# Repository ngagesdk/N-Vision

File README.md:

# N-Vision

**A modern replacement for the original Nokia N-Gage screen capture hardware.**

## Overview

N-Vision is an open-source hardware project that aims to recreate the functionality
of the extremely rare screen capture device that was once used by Nokia during
promotional events, game demonstrations, and for recording official N-Gage gameplay
footage.

As original capture units have become virtually impossible to find, preserving and
showcasing N-Gage software has become increasingly difficult. N-Vision provides a
modern alternative by tapping directly into the display interface without requiring
any modifications to the console itself.

The project uses a custom flexible PCB (FPC) that is installed between the N-Gage's
mainboard and LCD, allowing the display signals to be captured transparently.
A Raspberry Pi Pico 2 then decodes the display data in real time and outputs it over
DVI, making it suitable for recording, streaming, or development purposes.

## Features (Planned)

- Non-destructive installation using a custom flexible PCB
- Real-time LCD signal capture
- Display decoding on a Raspberry Pi Pico 2
- Digital DVI video output
- Open-source hardware and firmware
- Designed specifically for the Nokia N-Gage Classic

## Project Structure
 
| Directory              | Description                                                                                             |
| :--------------------- | :------------------------------------------------------------------------------------------------------ |
| [decoder/](decoder/)   | Proof-of-concept decoder to toy around with display signals.                                            |
| [firmware/](firmware/) | Firmware for the Raspberry Pi Pico 2 that captures and decodes the N-Gage display signals in real time. |
| [hardware/](hardware/) | Hardware design files for the custom flexible PCB that interfaces with the N-Gage display.              | 

## Project Status

> **This project is currently under active development and is not yet complete.**

The hardware, firmware, and documentation are all works in progress. Expect incomplete
features, design changes, and occasional breaking updates as development continues.

## Contributing

Contributions are warmly welcomed.

Whether you have experience with hardware design, embedded development, reverse
engineering, signal analysis, documentation, or simply own test hardware, your help
is greatly appreciated. Every contribution helps move the project closer to becoming
a practical and accessible replacement for the original capture hardware.

If you'd like to contribute, feel free to open an issue, start a discussion, or submit
a pull request.

## Goals

- Preserve the ability to capture authentic Nokia N-Gage gameplay.
- Provide an affordable and reproducible alternative to the original Nokia capture
  hardware.
- Document the N-Gage display interface for future preservation efforts.
- Build an open platform that the community can improve and extend.

## License

N-Vision is released under a dual-license model:

- **Software** (firmware, utilities, and related source code) is licensed under the
  [**MIT License**](firmware/LICENSE.md).
- **Hardware** (schematics, PCB layouts, mechanical designs, and other hardware design
  files) is licensed under the
  [**CERN Open Hardware Licence Version 2 - Permissive (CERN-OHL-P v2)**](hardware/cern_ohl_p_v2.txt).

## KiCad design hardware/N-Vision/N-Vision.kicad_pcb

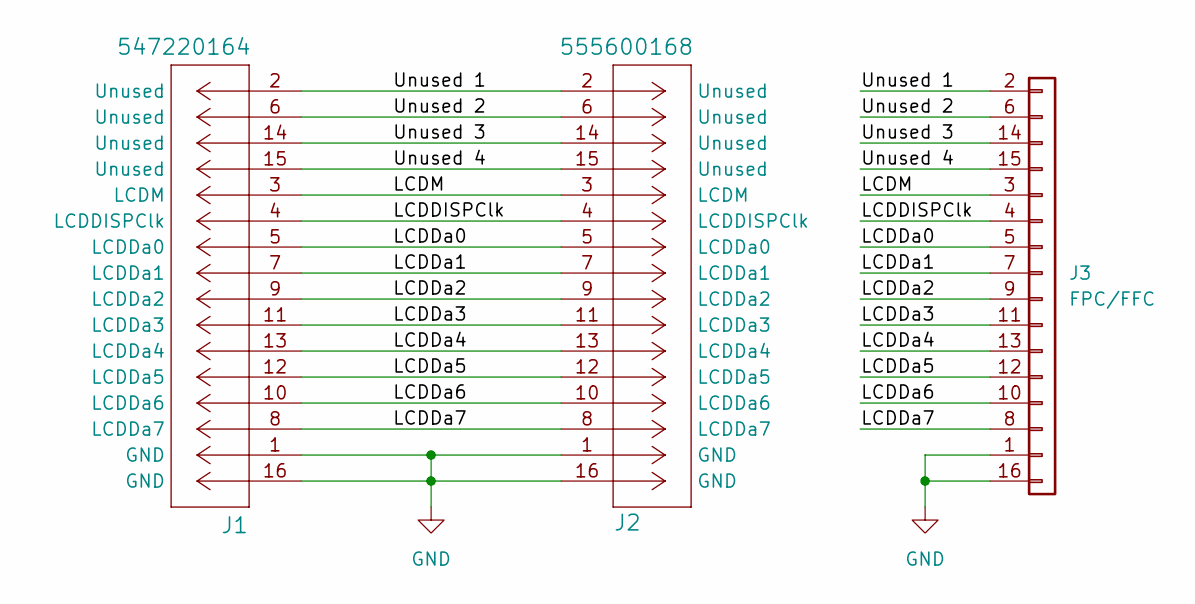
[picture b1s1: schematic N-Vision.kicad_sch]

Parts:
J1: 547220164; CONN_54722-0164_MOL
J2: 555600168; CONN_55560-0168_MOL
J3: FPC/FFC; FPC-16P-0.5mm

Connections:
/LCDDISPClk: J1.4 (LCDDISPClk), J2.4 (LCDDISPClk), J3.4
/LCDDa0: J1.5 (LCDDa0), J2.5 (LCDDa0), J3.5
/LCDDa1: J1.7 (LCDDa1), J2.7 (LCDDa1), J3.7
/LCDDa2: J1.9 (LCDDa2), J2.9 (LCDDa2), J3.9
/LCDDa3: J1.11 (LCDDa3), J2.11 (LCDDa3), J3.11
/LCDDa4: J1.13 (LCDDa4), J2.13 (LCDDa4), J3.13
/LCDDa5: J1.12 (LCDDa5), J2.12 (LCDDa5), J3.12
/LCDDa6: J1.10 (LCDDa6), J2.10 (LCDDa6), J3.10
/LCDDa7: J1.8 (LCDDa7), J2.8 (LCDDa7), J3.8
/LCDM: J1.3 (LCDM), J2.3 (LCDM), J3.3
/Unused 1: J1.2 (Unused), J2.2 (Unused), J3.2
/Unused 2: J1.6 (Unused), J2.6 (Unused), J3.6
/Unused 3: J1.14 (Unused), J2.14 (Unused), J3.14
/Unused 4: J1.15 (Unused), J2.15 (Unused), J3.15
GND: J1.1 (GND), J1.16 (GND), J2.1 (GND), J2.16 (GND), J3.1, J3.16

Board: 2 copper layers, 3 parts (2 on the bottom side), 15 nets, no tracks yet.

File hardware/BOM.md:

# Bill of materials

- [Molex 0555600168](https://www.molex.com/molex/products/part-detail/pcb_headers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  ([Digi-Key](https://www.digikey.com/short/nrwqm2ht))
- [Molex 0547220164](https://www.molex.com/molex/products/part-detail/pcb_recepta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 ([Digi-Key](https://www.digikey.com/short/298jd1bj))
- [Molex 5051101692](https://www.molex.com/en-us/products/part-detail/5051101692) ([Digi-Key](https://www.digikey.de/short/q1pv8zdh))

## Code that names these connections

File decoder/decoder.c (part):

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 *
 * ====================================================================== */
#define CH_LCDCLK 9  /* CSV column wired to LCDCLK                        */
#define CH_LCDM   1  /* CSV column wired to LCDM   (bus bit 7, mode flag) */
#define CH_LCDDa7 11 /* CSV column wired to LCDDa7 (bus bit 8)            */
#define CH_LCDDa6 12 /* CSV column wired to LCDDa6 (bus bit 6)            */
#define CH_LCDDa5 13 /* CSV column wired to LCDDa5 (bus bit 5)            */
#define CH_LCDDa4 6  /* CSV column wired to LCDDa4 (bus bit 4)            */
#define CH_LCDDa3 5  /* CSV column wired to LCDDa3 (bus bit 3)            */
#define CH_LCDDa2 4  /* CSV column wired to LCDDa2 (bus bit 2)            */
#define CH_LCDDa1 3  /* CSV column wired to LCDDa1 (bus bit 1)            */
#define CH_LCDDa0 2  /* CSV column wired to LCDDa0 (bus bit 0)            */

/* -----------------------------------------------------------------------
 * LCD bus signals:
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 *   LCDLLClk   0x75 – line-latch clock  (followed by target-row data words)
 *   LCDDISPClk 0x5C – display pixel clock (followed by pixel data words)
 * ----------------------------------------------------------------------- */
#define LCDM   0x80u /* LCDM mode flag (separate signal) */
#define LCDDa7 0x80u /* bit 7 */
#define LCDDa6 0x40u /* bit 6 */
#define LCDDa5 0x20u /* bit 5 */
#define LCDDa4 0x10u /* bit 4 */
#define LCDDa3 0x08u /* bit 3 */
#define LCDDa2 0x04u /* bit 2 */
#define LCDDa1 0x02u /* bit 1 */
#define LCDDa0 0x01u /* bit 0 */

#define LCDLLClk   0x75u /* line-latch clock strobe  (LCDM = 0)   */
#define LCDDISPClk 0x5Cu /* display pixel-clock strobe (LCDM = 0) */

/* Composite masks used in nibble decode */
#define LCD_PAYLOAD_MASK (LCDDa7 | LCDDa6 | LCDDa5 | LCDDa4 | LCDDa3 | LCDDa2 | LCDDa1 | LCDDa0) /* bits 7-0 */

#define MAX_CHANNELS 16
#define CSV_LINE_MAX 512
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

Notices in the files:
decoder/decoder.c:
Copyright (c) 2026, Michael Fitzmayer. All rights reserved.
SPDX-License-Identifier: MIT
